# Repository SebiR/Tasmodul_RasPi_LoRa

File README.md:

# Tasmodul Raspberry Pi + LoRa Concentrator
A 100x100mm "Tasmodul" PCB for a Raspberry Pi with the option to populate a LoRaWAN mini PCIe card to work as a LoraWAN gateway

## Features
* Wide inpult voltage range from 8 to 40V
* Mini-PCIe Slot for LoraWAN concentrator modules like the Seeed WM1302 or the RAK2287
* Optional Quectel L76 GPS module
* Optional small fan controlled by the Raspberry Pi
* Ideal for ChirpStack OS

## GPS

## SMA Connectors
Although there's the option to use short U.fl to U.fl connectors, I recommend using those THT SMA connectors with built-in pigtail:

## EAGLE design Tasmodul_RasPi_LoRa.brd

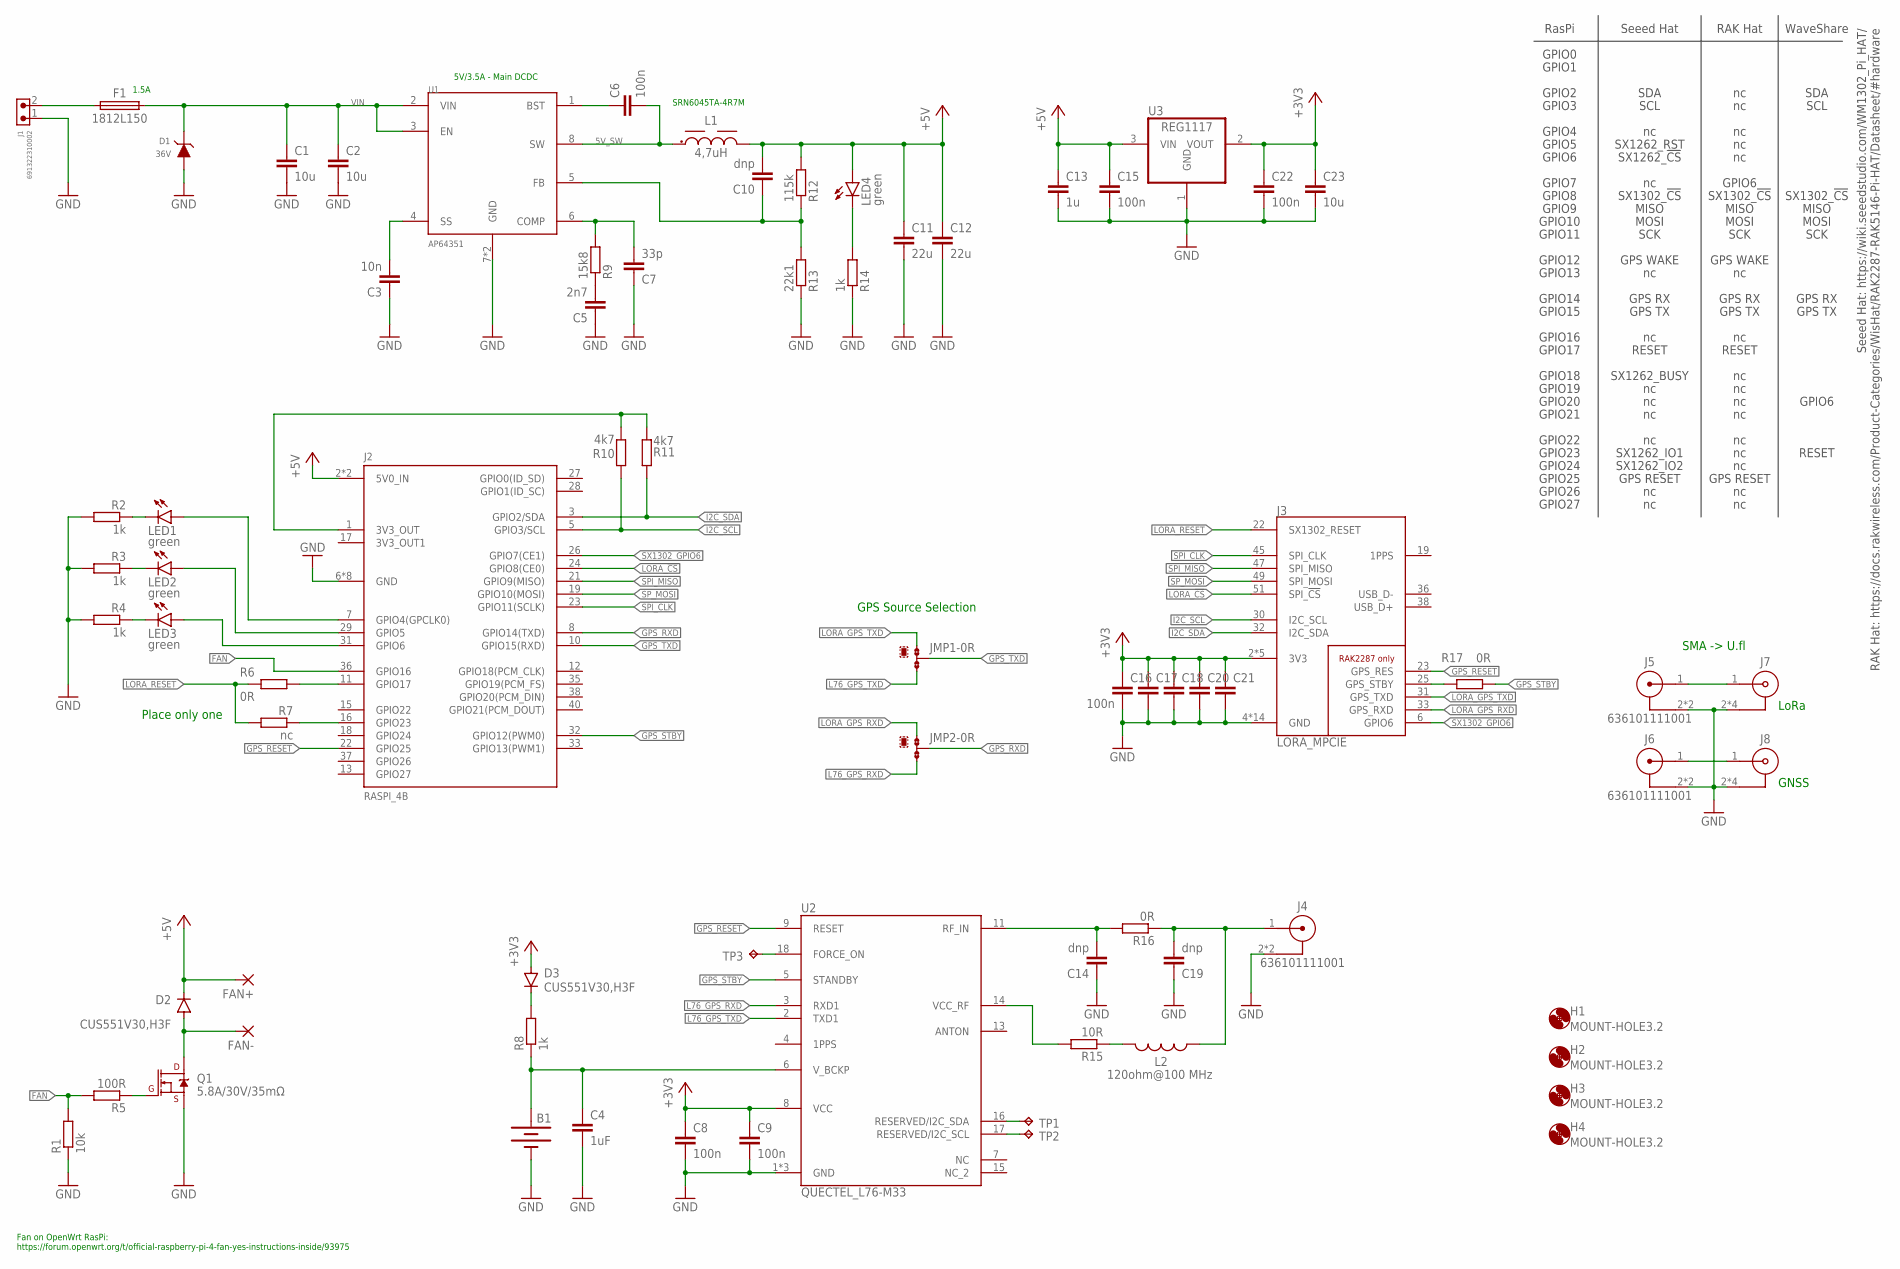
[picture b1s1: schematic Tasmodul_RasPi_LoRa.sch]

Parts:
B1: 6.8MM_COIN_CELL; ML414H_IV01E
C1, C2: 10u; C1206
C3: 10n; C0603
C4: 1uF; C0603
C5: 2n7; C0603
C6, C8, C9, C15, C16, C17, C18, C20, C21, C22: 100n; C0603
C7: 33p; C0603
C10, C14, C19: dnp; C0603
C11, C12: 22u; C0805
C13: 1u; C0603
C23: 10u; C0603
D1: 36V; WE-TVSP_DO-214AC_UNIDIRECTIONAL
D2, D3: CUS551V30,H3F; SOD323-R
F1: 1812L150; FUSC4532X125
FAN+: 1,6/0,8
FAN-: 1,6/0,8
H1, H2, H3, H4: MOUNT-HOLE3.2; 3,2
J1: 691322310002
J2: RASPI_4B; RASPI_4B_FLIPPED_SMD
J3: LORA_MPCIE; MINI_PCIE_CONNECTOR_5.2H
J4, J5, J6: 636101111001
J7, J8: 60311002111526
JMP1, JMP2: 0R-JUMPA; A0R-JMP
L1: 4,7uH; WE-LQS_6045
L2: 120ohm@100 MHz; WE-CBF_0603_W2.2
LED1, LED2, LED3, LED4: green; CHIPLED_0603
Q1: 5.8A/30V/35mΩ; SOT23-3
R1: 10k; R0603
R2, R3, R4, R8, R14: 1k; R0603
R5: 100R; R0603
R6, R16, R17: 0R; R0603
R7: nc; R0603
R9: 15k8; R0603
R10, R11: 4k7; R0603
R12: 115k; R0603
R13: 22k1; R0603
R15: 10R; R0603
TP1, TP2, TP3: TPTP15R; TP15R
U1: AP64351; SOIC8-EP
U2: QUECTEL_L76-M33; L76_QWS
U3: REG1117; SOT223

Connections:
5V_SW: C6.2, L1.1, U1.8 (SW)
+3V3: C8.1, C9.1, C16.1, C17.1, C18.1, C20.1, C21.1, C22.1, C23.1, D3.A, J3.2 (3V3), J3.24 (3V3), J3.39 (3V3), J3.41 (3V3), J3.52 (3V3), U2.8 (VCC), U3.2 (VOUT)
+5V: C10.2, C11.1, C12.1, C13.1, C15.1, D2.C, FAN+.1, J2.2 (5V0_IN), J2.4 (5V0_IN), L1.2, LED4.A, R12.2, U3.3 (VIN)
FAN: J2.36 (GPIO16), R1.2, R5.2
GND: B1.-, C1.2, C2.2, C3.1, C4.2, C5.1, C7.1, C8.2, C9.2, C11.2, C12.2, C13.2, C14.1, C15.2, C16.2, C17.2, C18.2, C19.1, C20.2, C21.2, C22.2, C23.2, D1.2 (A), J1.1, J2.6 (GND), J2.9 (GND), J2.14 (GND), J2.20 (GND), J2.25 (GND), J2.30 (GND), J2.34 (GND), J2.39 (GND), J3.4 (GND), J3.9 (GND), J3.15 (GND), J3.18 (GND), J3.21 (GND), J3.26 (GND), J3.27 (GND), J3.29 (GND), J3.34 (GND), J3.35 (GND), J3.37 (GND), J3.40 (GND), J3.43 (GND), J3.50 (GND), J4.2, J4.3 (2), J5.2, J5.3 (2), J6.2, J6.3 (2), J7.2, J7.3 (2), J7.4 (2), J7.5 (2), J8.2, J8.3 (2), J8.4 (2), J8.5 (2), Q1.2 (S), R1.1, R2.2, R3.2, R4.2, R13.1, R14.1, U1.7 (GND), U1.9 (GND), U2.1 (GND), U2.10 (GND), U2.12 (GND), U3.1 (GND)
GPS_RESET: J2.22 (GPIO25), J3.23 (GPS_RES), U2.9 (RESET)
GPS_RXD: J2.8 (GPIO14(TXD)), JMP2.2
GPS_STBY: J2.32 (GPIO12(PWM0)), R17.1, U2.5 (STANDBY)
GPS_TXD: J2.10 (GPIO15(RXD)), JMP1.2
HF_GNSS: J6.1, J8.1
HF_LORA: J5.1, J7.1
I2C_SCL: J2.5 (GPIO3/SCL), J3.30 (I2C_SCL), R10.1
I2C_SDA: J2.3 (GPIO2/SDA), J3.32 (I2C_SDA), R11.1
L76_GPS_RXD: JMP2.3, U2.3 (RXD1)
L76_GPS_TXD: JMP1.3, U2.2 (TXD1)
LORA_!CS: J2.24 (GPIO8(CE0)), J3.51 (SPI_!CS)
LORA_GPS_RXD: J3.33 (GPS_RXD), JMP2.1
LORA_GPS_TXD: J3.31 (GPS_TXD), JMP1.1
LORA_RESET: J3.22 (SX1302_RESET), R6.2, R7.2
unnamed: J2.16 (GPIO23), R7.1
unnamed: C3.2, U1.4 (SS)
unnamed: J2.11 (GPIO17), R6.1
unnamed: L2.2, R15.1
unnamed: C6.1, U1.1 (BST)
unnamed: C10.1, R12.1, R13.2, U1.5 (FB)
unnamed: LED4.C, R14.2
unnamed: D3.C, R8.2
unnamed: Q1.1 (G), R5.1
unnamed: R15.2, U2.14 (VCC_RF)
unnamed: C5.2, R9.1
unnamed: C7.2, R9.2, U1.6 (COMP)
unnamed: J2.1 (3V3_OUT), R10.2, R11.2
unnamed: D2.A, FAN-.1, Q1.3 (D)
unnamed: F1.1, J1.2
unnamed: TP1.TP, U2.16 (RESERVED/I2C_SDA)
unnamed: TP2.TP, U2.17 (RESERVED/I2C_SCL)
unnamed: TP3.TP, U2.18 (FORCE_ON)
unnamed: J3.25 (GPS_STBY), R17.2
unnamed: LED1.C, R2.1
unnamed: LED2.C, R3.1
unnamed: LED3.C, R4.1
unnamed: J2.7 (GPIO4(GPCLK0)), LED1.A
unnamed: J2.29 (GPIO5), LED2.A
unnamed: J2.31 (GPIO6), LED3.A
RF_CON: C19.2, J4.1, L2.1, R16.1
RF_MATCHED: C14.2, R16.2, U2.11 (RF_IN)
SPI_CLK: J2.23 (GPIO11(SCLK)), J3.45 (SPI_CLK)
SPI_MISO: J2.21 (GPIO9(MISO)), J3.47 (SPI_MISO)
SP_MOSI: J2.19 (GPIO10(MOSI)), J3.49 (SPI_MOSI)
SX1302_GPIO6: J2.26 (GPIO7(CE1)), J3.6 (GPIO6)
VBAT: B1.+, C4.1, R8.1, U2.6 (V_BCKP)
VIN: C1.1, C2.1, D1.1 (C), F1.2, U1.2 (VIN), U1.3 (EN)

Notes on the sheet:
GPIO0
GPIO1
GPIO2
GPIO3
GPIO4
GPIO5
GPIO6
GPIO7
GPIO8
GPIO9
GPIO10
GPIO11
GPIO12
GPIO13
GPIO14
GPIO15
GPIO16
GPIO17
GPIO18
GPIO19
GPIO20
GPIO21
GPIO22
GPIO23
GPIO24
GPIO25
GPIO26
GPIO27
Seeed Hat
RasPi
RAK Hat
SCL
SDA
GPS RX
GPS TX
RESET
SX1262_BUSY
MOSI
MISO
SCK

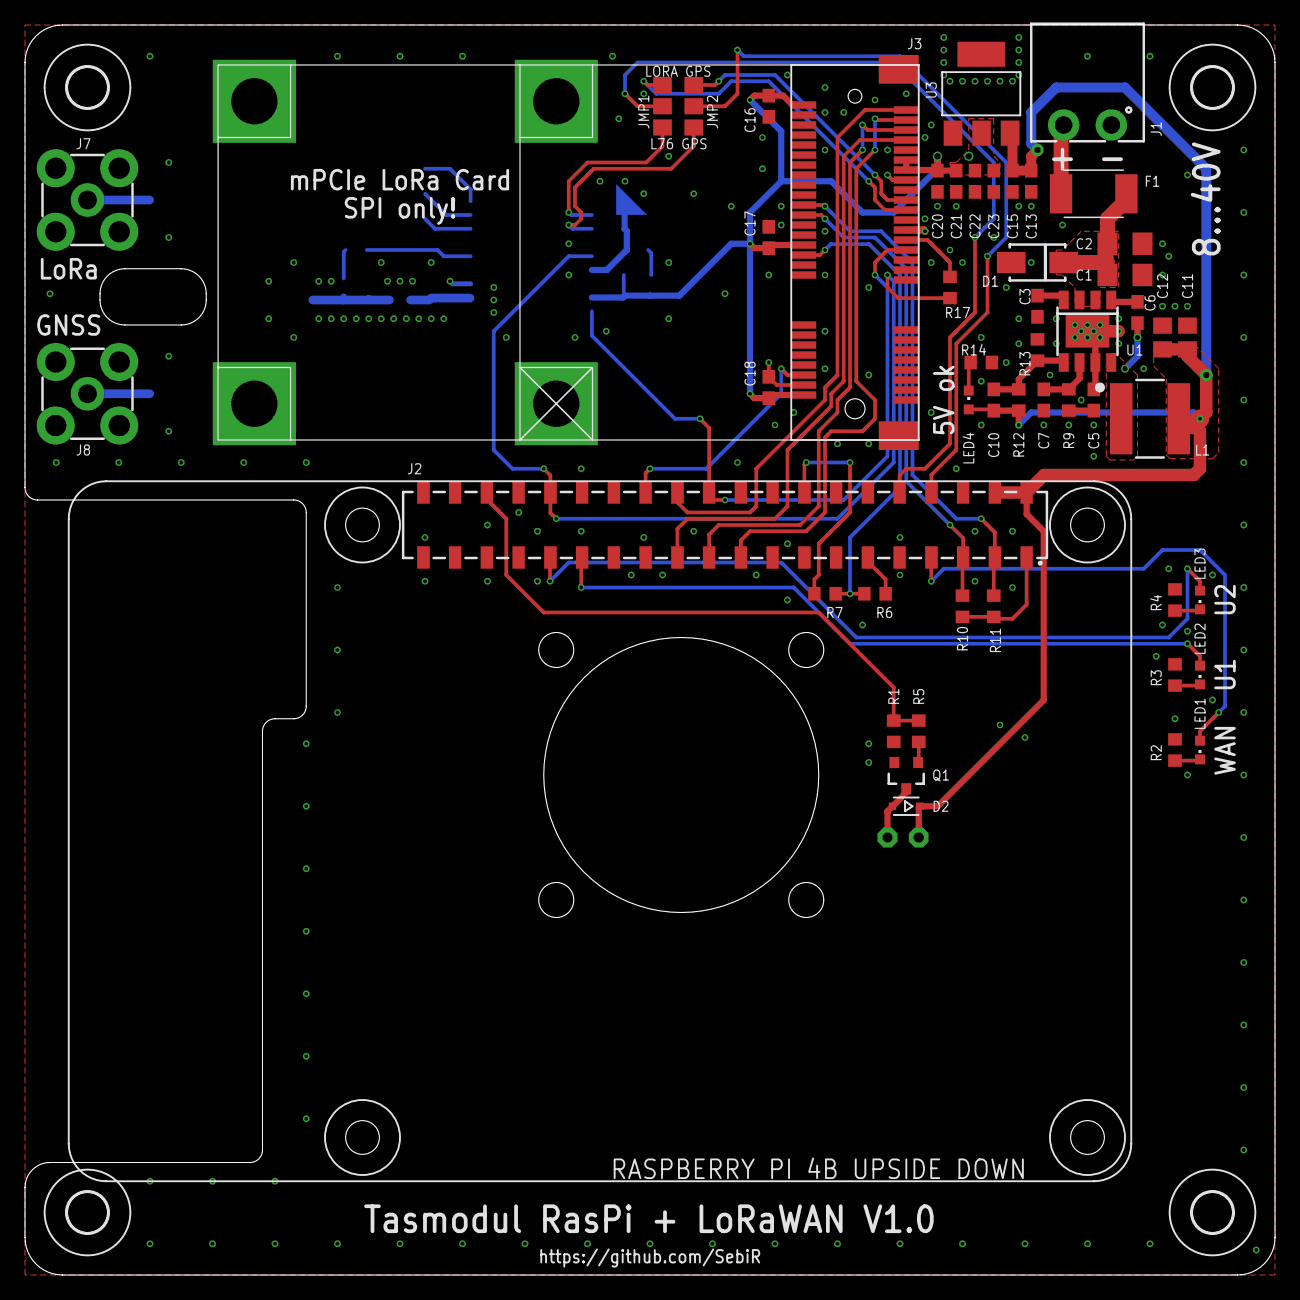
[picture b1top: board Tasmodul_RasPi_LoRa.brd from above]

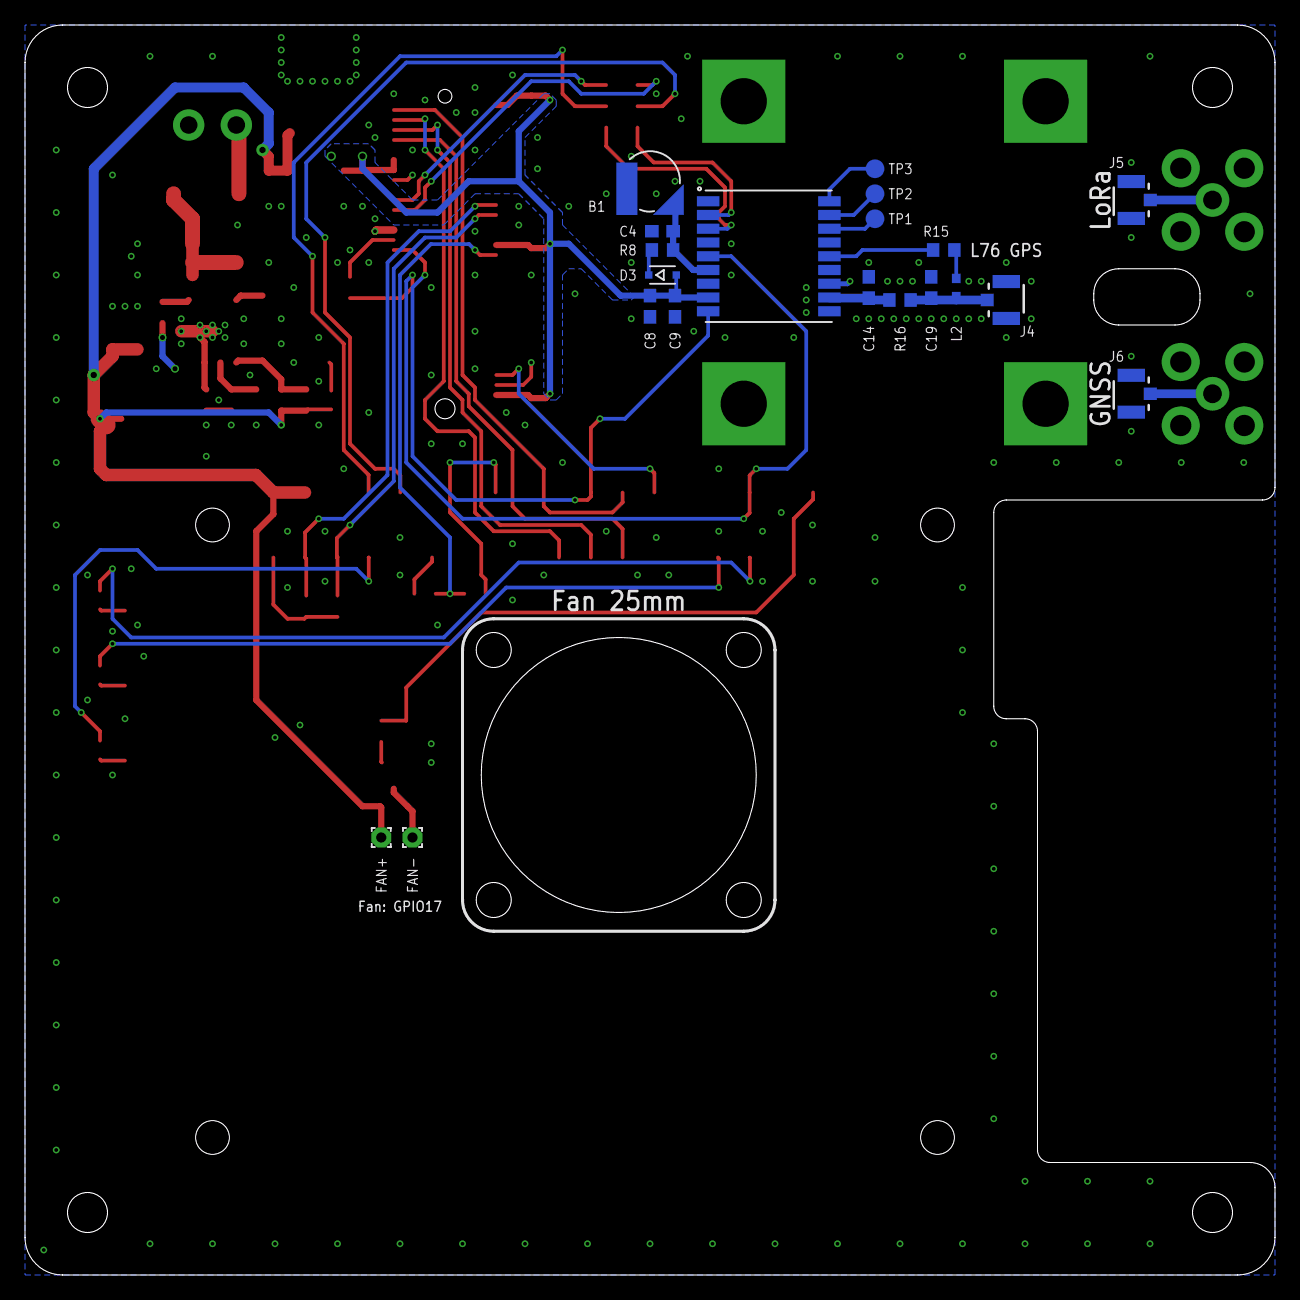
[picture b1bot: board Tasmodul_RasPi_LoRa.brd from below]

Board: 2 copper layers, 100.0 x 100.0 mm, 75 parts (21 on the bottom side), 52 nets.

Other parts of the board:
U$1: FAN_25MM

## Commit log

2024-03-02 * Added more description to the schematic * Added more silk screen information to the PCB * Added U.fl connectors for the SMA connectors as a backup
2024-03-03 * Added multifuse to power input * Added I2C pullup resistors * Added test points to unused GPS module pins * Updated README.md
2024-03-04 * Added 3 status LEDs to the RasPi * Minor Layout tweaks

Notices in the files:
parts and their libraries:
Wurth_Connectors_WR-TBL Pluggable Connec: Copyright: Würth Elektronik
SparkFun-Batteries: Licensing: Creative Commons ShareAlike 4.0 International - https://creativecommons.org/licenses/by-sa/4.0
